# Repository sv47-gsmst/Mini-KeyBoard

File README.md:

# My 9‑Key Macropad  
This is my submission for a custom 9‑key macropad built using the XIAO RP2040, Cherry‑style switches, and a fully custom PCB + case.

---

### Inspiration

I wanted to create a macropad that was both functional and clean — something I could use every day for shortcuts, media controls, and quick actions. Designing the PCB, case, and firmware myself made the whole project feel like a complete end‑to‑end build.

---

### Challenges

This project pushed me in a few areas:

- Getting the PCB routed neatly in KiCad  
- Making sure the XIAO RP2040 pinout matched my switch wiring  
- Learning how to model and align everything in Fusion 360  
- Ensuring the case fit perfectly around the PCB, switches, and USB port  

Even with the challenges, I’m proud of how polished the final macropad turned out.

---

### Specifications

**BOM:**  
- 9× Cherry MX‑style switches  
- 1× XIAO RP2040  
- 9× Keycaps  
- 2× SK6812 MINI LEDs  
- 4× M3x16 bolts  
- 4× M3 heatsets  

**Others:**  
- KMK Firmware  
- `main.py`  
- Top Case `.stl`  
- Bottom Case `.stl`  
- KiCad Schematic  
- KiCad PCB  

---

Schematic | PCB | Case
:-------------------------:|:-------------------------:|:-------------------------:
 |  | 

---

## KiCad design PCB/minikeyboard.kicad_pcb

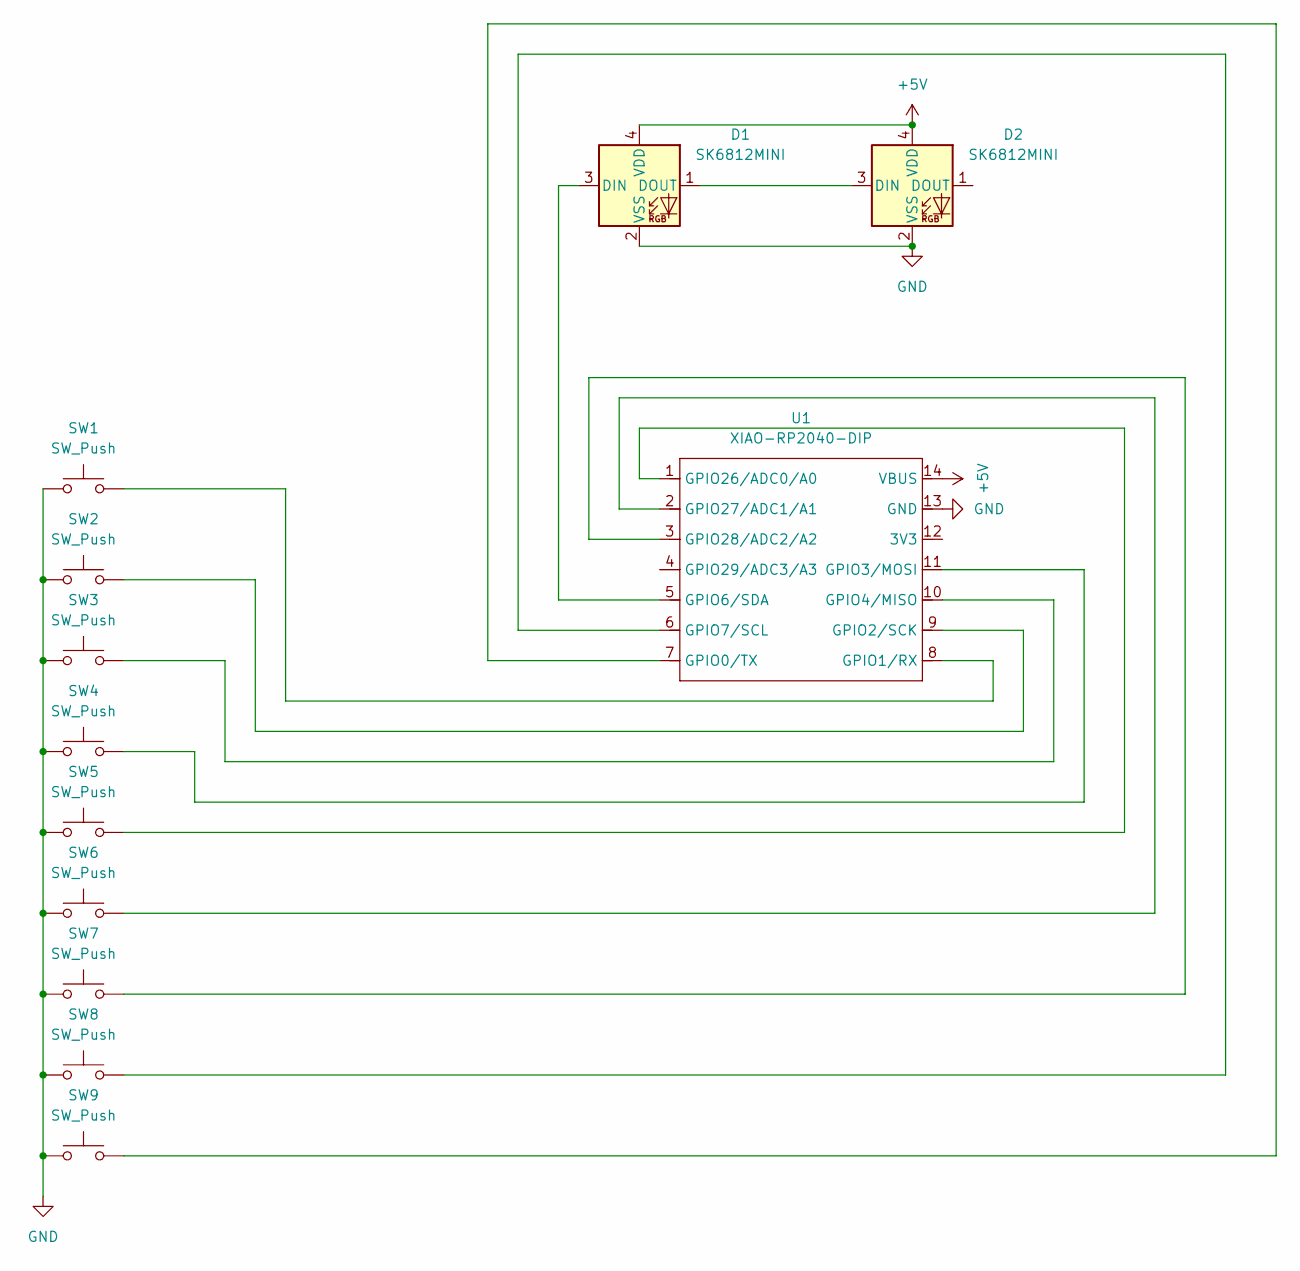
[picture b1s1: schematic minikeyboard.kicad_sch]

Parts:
D1, D2: SK6812MINI; LED_SK6812MINI_PLCC4_3.5x3.5mm_P1.75mm
SW1, SW2, SW3, SW4, SW5, SW6, SW7, SW8, SW9: SW_Push; SW_Cherry_MX_1.00u_PCB
U1: XIAO-RP2040-DIP

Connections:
+5V: D1.4 (VDD), D2.4 (VDD), U1.14 (VBUS)
GND: D1.2 (VSS), D2.2 (VSS), SW1.1, SW2.1, SW3.1, SW4.1, SW5.1, SW6.1, SW7.1, SW8.1, SW9.1, U1.13 (GND)
unnamed: D1.3 (DIN), U1.5 (GPIO6/SDA)
unnamed: D1.1 (DOUT), D2.3 (DIN)
unnamed: SW9.2, U1.7 (GPIO0/TX)
unnamed: SW1.2, U1.8 (GPIO1/RX)
unnamed: SW2.2, U1.9 (GPIO2/SCK)
unnamed: SW4.2, U1.11 (GPIO3/MOSI)
unnamed: SW3.2, U1.10 (GPIO4/MISO)
unnamed: SW8.2, U1.6 (GPIO7/SCL)
unnamed: SW5.2, U1.1 (GPIO26/ADC0/A0)
unnamed: SW6.2, U1.2 (GPIO27/ADC1/A1)
unnamed: SW7.2, U1.3 (GPIO28/ADC2/A2)

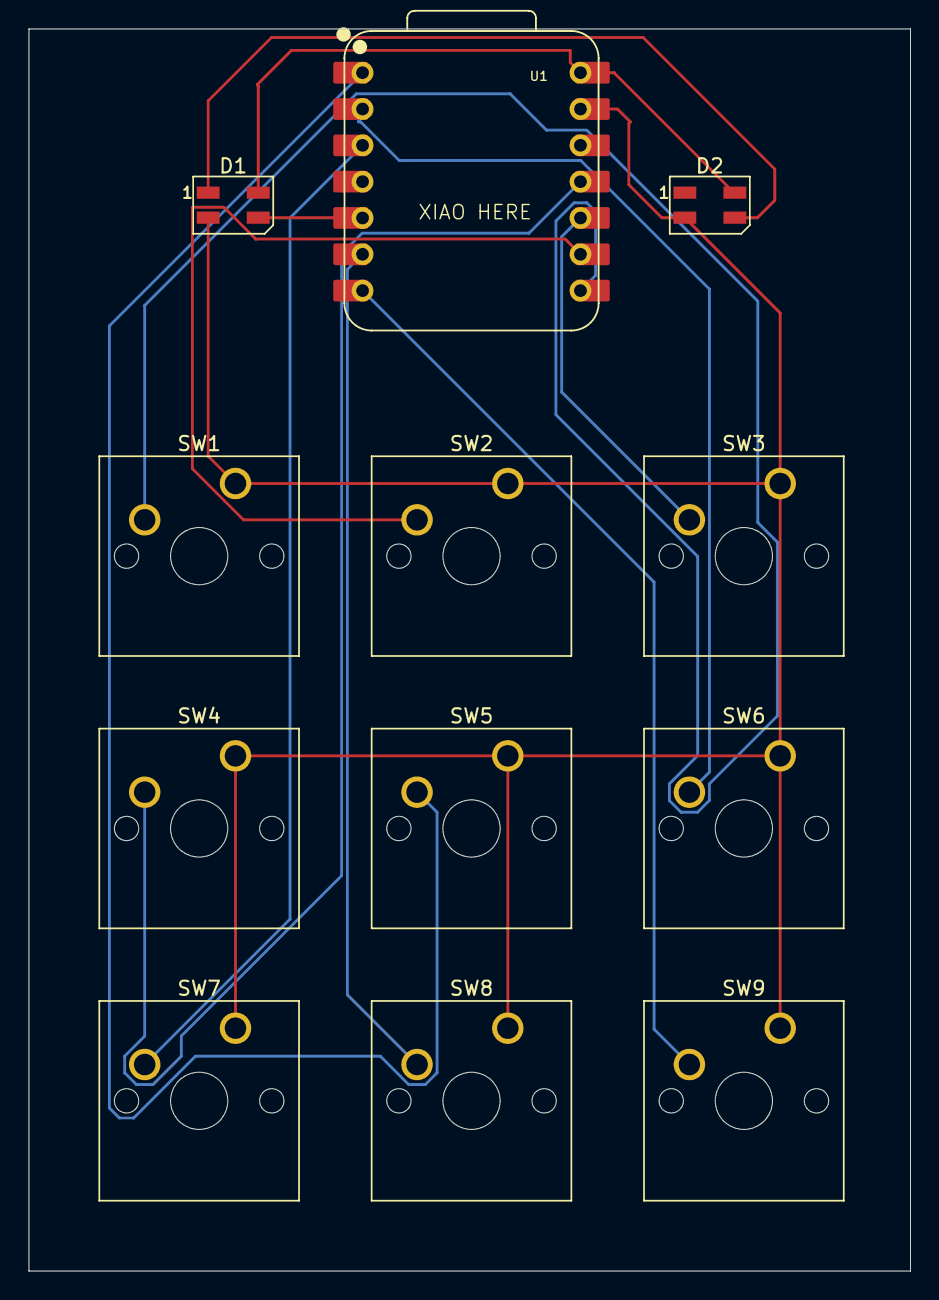
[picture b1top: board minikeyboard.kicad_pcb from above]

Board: 2 copper layers, 61.7 x 86.9 mm, 12 parts (0 on the bottom side), 13 nets.

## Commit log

2025-12-30 Create Mini Keyboard Top
2025-12-30 Create s
2025-12-30 Create e
